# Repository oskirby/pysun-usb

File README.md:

PySUN-USB
=========
The PySUN is a USB dongle for IEEE 802.15.4 Smart Utility Networking protocols. This project is based around
an STM32F4-series microprocessor and the Atmel/Microchip AT86RF215 dual-band IEEE 802.15.4 transceiver. This
board also supports a Micropython programming environment. The two RF bands from the transceiver are combined
into a single antenna port using an RF diplexer.

This board is released as an Open Source Hardware project, including the full PCB design files from KiCAD.

Features
-----------
Attached to the STM32F4 microcontroller, are the following peripherals:
* AT86RF215 connected to SPI2.
* 32Mbit SPI flash connected to SPI1.
* RGB LED connected to PB0, PB1 and PB10.
* Tactile switch connected to BOOT0 and PB7.
* Power/status LED connected to PB6.

Castellated edges are provided, exposing:
* SPI1
* I2C1
* USART1
* RF215 FEA and FEB outputs

Power is provided by a 2MHz synchronous buck regulator and the clock reference is provided from a 26MHz TCXO.

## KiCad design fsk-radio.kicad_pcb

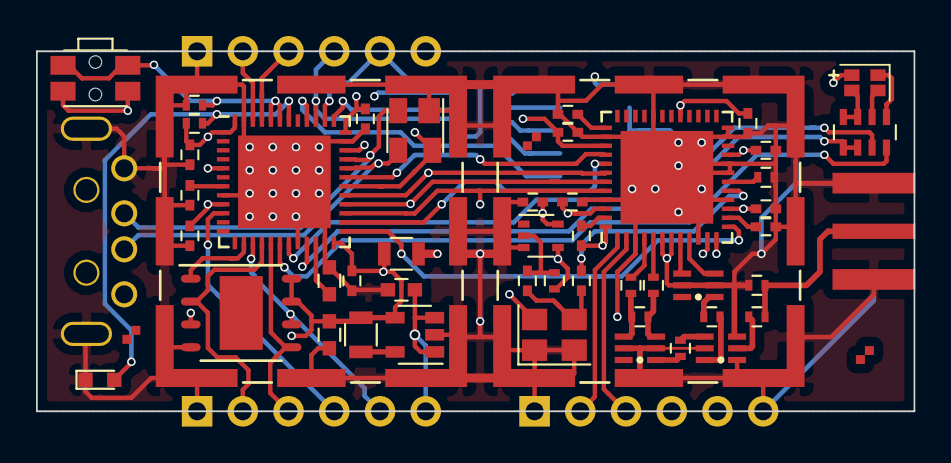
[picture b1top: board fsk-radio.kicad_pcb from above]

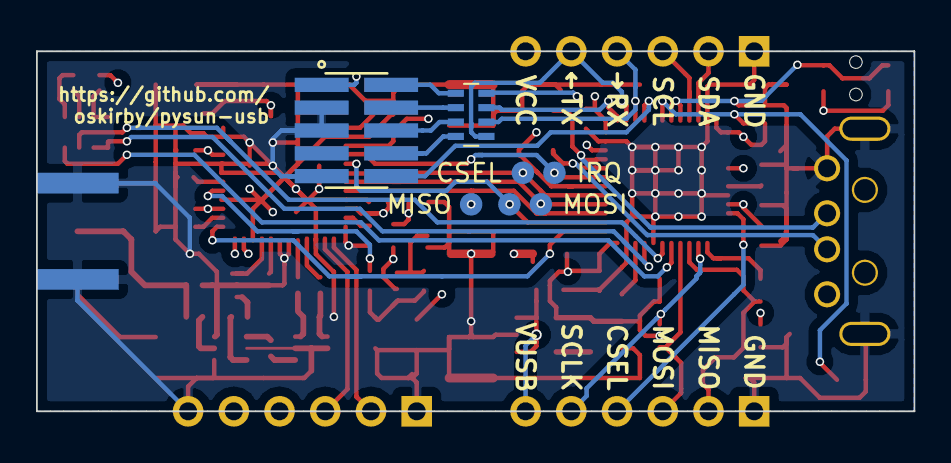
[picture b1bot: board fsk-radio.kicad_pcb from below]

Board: 4 copper layers, 48.8 x 20.0 mm, 65 parts (10 on the bottom side), 63 nets.

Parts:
B9: 0896BM15E0025; Balun_0805
B24: 2450FB15A050; Balun_0805
C3, C7, C11: 4.7u; C_0603
C4, C5, C6, C8, C10, C17: 100n; C_0402
C9, C15: 1n; C_0402
C19, C20, C21, C22, C23, C24, C25, C28: C; C_0402
C26: 0.8pF; L_0402
C27, C29: 15pF; L_0402
C31, C32: 1.8p; L_0402
D1: LED_RGB_ANODE; LED_0606_RGB
D2: PRTR5V0U2X; SOT-143
D3: LED; LED_0603
FID1, FID2, FID2#2: Fiducial_1mm_Dia_2.54mm_Outer_CopperTop; Fiducial_1mm_checker_1.5mm_mask
IC1: STM32F4xx-QFN48; QFN-48-1EP_7x7mm_Pitch0.5mm
IC2: AT86RF215; QFN-48-1EP_7x7mm_Pitch0.5mm
IC3: LM3671; SOT-23-5
IC4: NC7SZ04; SOT-353_SC-70-5
IC6: W25Q32BVZPIP; DFN-S-8-1EP_6x5mm_Pitch1.27mm
IC7: DPX202700DT; Balun_0805
IRQ1: TEST; Measurement_Point_Round-SMD-Pad_XSmall
J1: USB_A; CUI-UP2-AH-TH
J2, J6, J8: Conn_01x06; Castellated_Edge_6pin_2.54mm
J3: CONN_02X05; ftsh-105-01-dv
J4, J5: RF_Shield_One_Piece; Laird_Technologies_BMI-S-102_16.50x16.50mm_Paste
J7: SMA; SMA-Board-Edge
L1: 2.2u; L_0805
L2: 5.6n; L_0402
MISO1: TEST; Measurement_Point_Round-SMD-Pad_XSmall
MOSI1: TEST; Measurement_Point_Round-SMD-Pad_XSmall
R1, R17: 10k; R_0402
R2: 270; R_0402
R3, R4: R; R_0402
R5: 0; R_0805
RN1: 330; R_Array_Concave_4x0603
RN3: 22; R_Array_Concave_4x0603
SCLK1: TEST; Measurement_Point_Round-SMD-Pad_XSmall
SW1: SW_Push; SW_SPST_EVQP7C
X1: TXETBLSANF-26; Crystal_SMD_3225-4pin_3.2x2.5mm
exegin-logo: exegin-logo; exegin-logo-mask
oshw-silks: G***; oshw-mask
oshw-text: G***; oshw-text

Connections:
+5V: C7.1, D2.4, IC1.30, IC3.1, IC3.3, J1.1, J6.6
/CPU/BLUE: IC1.21, RN1.1, RN1.2
/CPU/FL_MISO: IC1.16, IC6.2, J6.2
/CPU/FL_MOSI: IC1.17, IC6.5, J6.3
/CPU/FL_SCLK: IC1.15, IC6.6, J6.5
/CPU/GREEN: IC1.19, RN1.3
/CPU/RED: IC1.18, RN1.4
/CPU/RF_CLK: C15.1, IC2.17
/CPU/RF_IRQ: IC1.31, IC2.40, IRQ1.1
/CPU/RXD_IN: IC1.39, J2.4, RN3.2
/CPU/SCL: IC1.45, J2.3
/CPU/SDA: IC1.46, J2.2
/CPU/SPI_CLK: IC1.26, IC2.41, SCLK1.1
/CPU/SPI_MISO: IC1.27, IC2.44, MISO1.1
/CPU/SPI_MOSI: IC1.28, IC2.43, MOSI1.1
/CPU/STATUS: D3.2, IC1.42, R2.2
/CPU/SWITCH: IC1.43, IC1.44, R1.1, SW1.2
/CPU/TXD_OUT: IC1.38, J2.5, RN3.1
/CPU/USB+: D2.2, IC1.33, J1.3
/CPU/USB-: D2.3, IC1.32, J1.2
/CPU/~EXT_CSEL: IC1.10, J6.4
/CPU/~FL_CSEL: IC1.14, IC6.1
/CPU/~RF_NRST: IC1.25, IC2.13
/CPU/~SPI_CS: IC1.29, IC2.42
/RF/FEA09: IC2.11, J8.4
/RF/FEA24: IC2.1, J8.2
/RF/FEB09: IC2.12, J8.5
/RF/FEB24: IC2.2, J8.3
/RF/RF09+: B9.4, IC2.8
/RF/RF09-: B9.3, IC2.9
/RF/RF24+: C32.2, IC2.4
/RF/RF24-: C31.1, IC2.5
GND: B9.2, B9.5, B24.2, B24.5, C3.2, C4.1, C5.2, C6.2, C7.2, C8.2, C10.2, C11.2, C17.1, C19.2, C20.2, C21.1, C22.2, C23.2, C24.2, C25.2, C28.2, D2.1, D3.1, IC1.8, IC1.20, IC1.23, IC1.35, IC1.47, IC1.49, IC2.3, IC2.6, IC2.7, IC2.10, IC2.16, IC2.19, IC2.20, IC2.23, IC2.24, IC2.32, IC2.38, IC2.45, IC2.48, IC2.49, IC3.2, IC4.3, IC6.4, IC7.1, IC7.3, IC7.5, J1.4, J1.5, J2.1, J3.3, J3.5, J3.9, J4.1, J5.1, J6.1, J7.2, J8.1, J8.6, R1.2, R4.2, R17.2, X1.1, X1.2
unnamed: B9.1, C27.2
unnamed: B24.1, C26.1
unnamed: B24.3, C31.2, L2.1
unnamed: B24.4, C32.1, L2.2
unnamed: C4.2, IC1.7
unnamed: C9.1, IC4.2, R3.2
unnamed: C11.1, IC1.22
unnamed: C9.2, C15.2, X1.3
unnamed: C19.1, IC2.14
unnamed: C20.1, IC2.47
unnamed: C21.2, IC2.37
unnamed: C26.2, IC7.4
unnamed: C27.1, IC7.6
unnamed: C29.1, J7.1, R17.1
unnamed: C29.2, IC7.2
unnamed: D1.B, RN1.7, RN1.8
unnamed: D1.G, RN1.6
unnamed: D1.R, RN1.5
unnamed: IC1.5, IC4.4, R3.1
unnamed: IC1.34, RN3.4
unnamed: IC1.37, RN3.3
unnamed: IC1.40, J3.10
unnamed: IC2.18, R4.1
unnamed: IC3.5, L1.1
unnamed: J3.2, RN3.5
unnamed: J3.4, RN3.6
unnamed: J3.6, RN3.7
unnamed: J3.8, RN3.8
VCC: C3.1, C5.1, C6.1, C8.1, C10.1, C17.2, D1.A, IC1.1, IC1.9, IC1.24, IC1.36, IC1.48, IC3.4, IC4.5, IC6.3, IC6.7, IC6.8, J2.6, J3.1, L1.2, R2.1, R5.2, SW1.1, X1.4
VDD: C22.1, C23.1, C24.1, C25.1, C28.1, IC2.15, IC2.21, IC2.29, IC2.39, IC2.46, R5.1

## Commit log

2017-08-16 Add KiCAD design files.
2017-08-16 Add 3D renders of PCB
2017-08-17 Cleanup silkscreen, add status LED.
2017-08-26 Move CLKEN to BOOT1 pin to enable the TCXO during DFU boot.
2017-08-30 Release for manufacturing.
2018-04-08 Rework and revise for revision 2.
    Major changes include:
    - Refactor clock heirarchy to improve RF performance.
    - Add pushbutton switch and SPI flash.
    - Shrink board dimensions down to make it more of a usable dongle.
    - Eliminate u.FL test points and SPI test pads.
    - Convert pin headers to castellated edges.
2018-04-12 Add more test features to the RF section.
    Split the RF and CPU power nets and connect them via a zero-ohm jumper
    to allow current sense, and add test pads for the RF SPI bus.
2018-04-13 Release to manufacturing: rev2 prototype.
2018-04-14 Add spreadsheet for BOM.
2018-04-22 Add copyright and README.
2018-04-22 Move 3D models into common repository.
2018-04-25 Final update to PCB for manufacturing release.
    Capacitor C22 moved to improve clearance with the RF shield and switch
    to using checker-mark pattern for fiducials. Other minor adjustments to
    the fab reference, silkscreen and paste layers.
